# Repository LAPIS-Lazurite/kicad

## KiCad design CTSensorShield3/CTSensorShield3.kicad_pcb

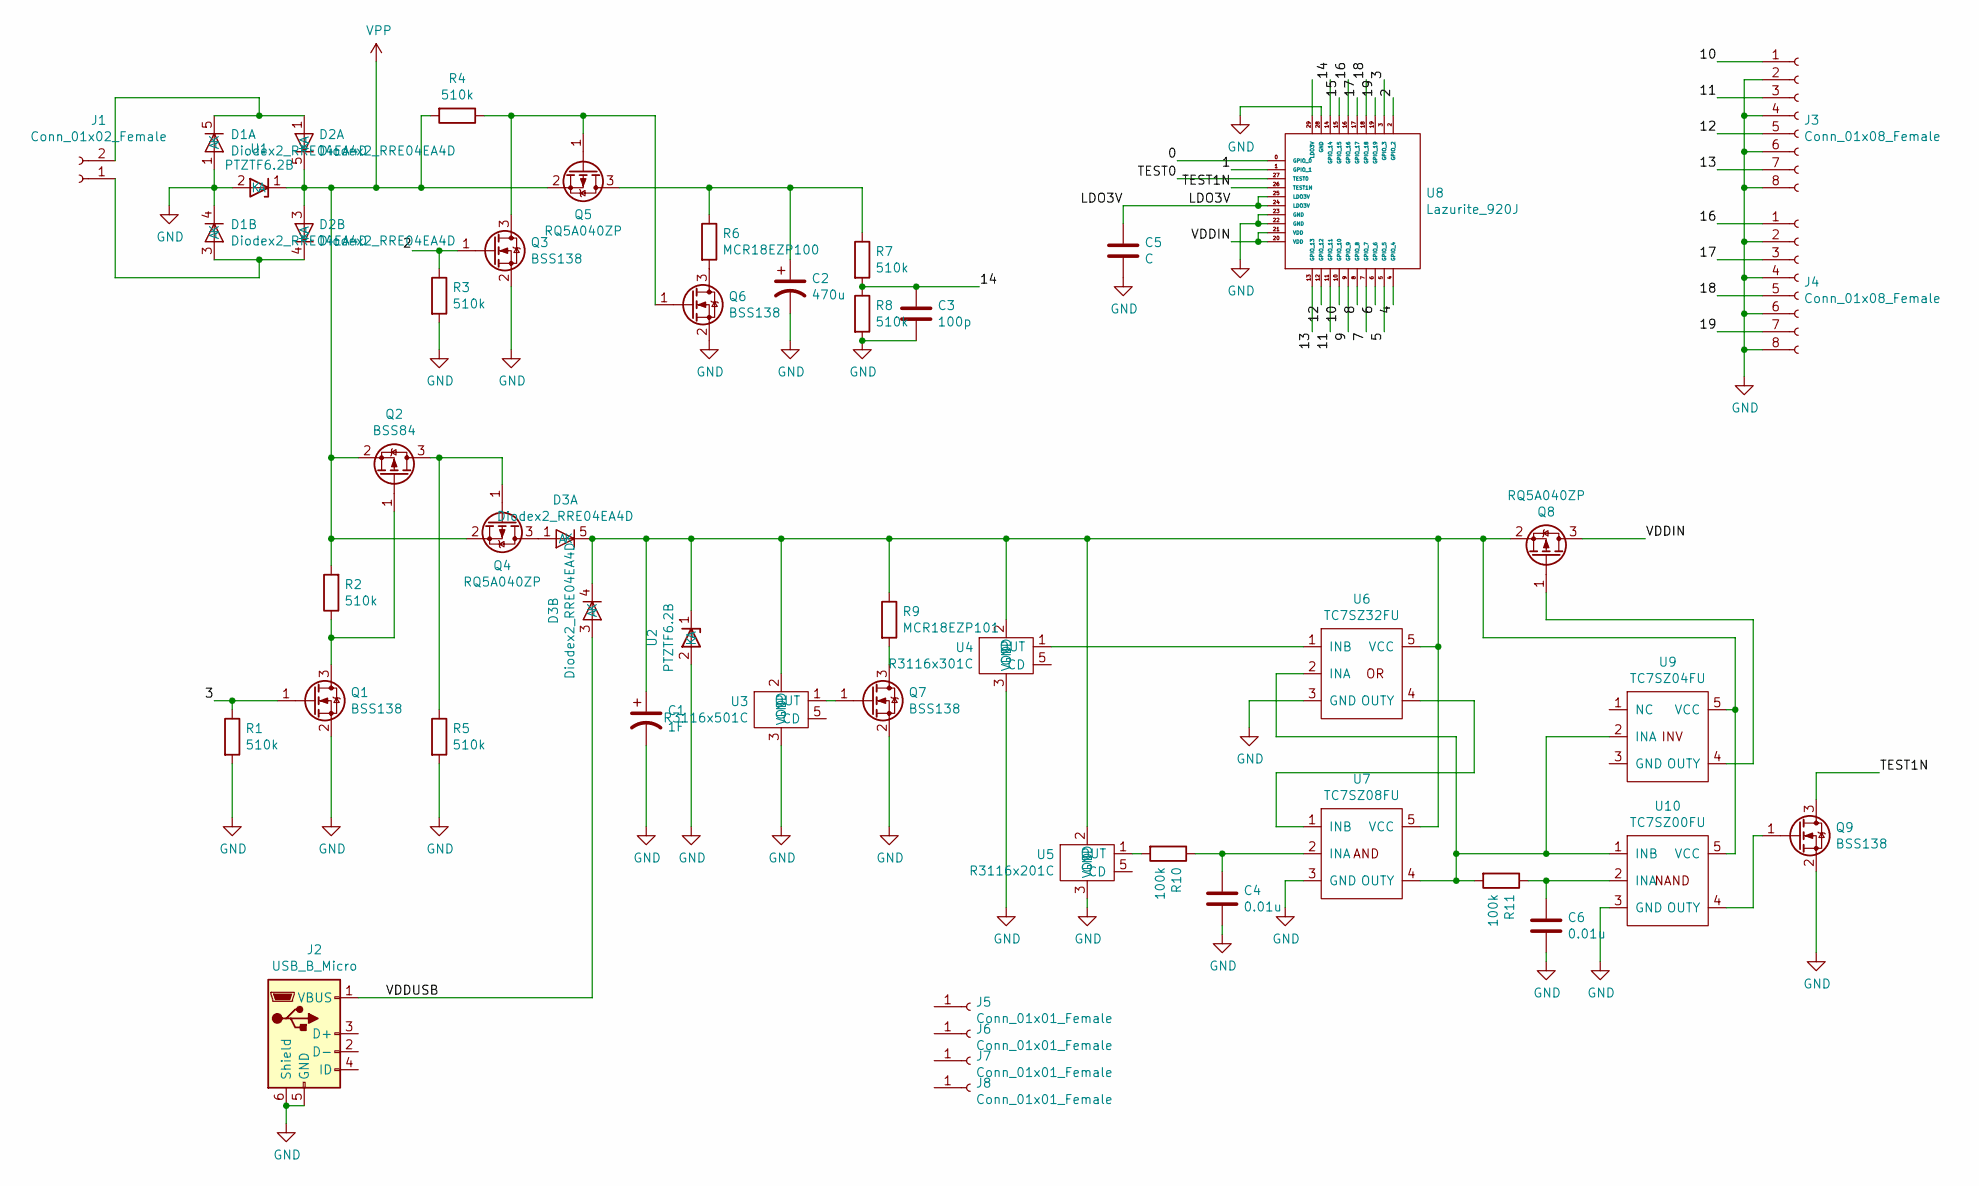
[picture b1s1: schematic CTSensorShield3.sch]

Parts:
C1: 1F; CP_Radial_D20.5mm_P5.50mm
C2: 470u; CP_Radial_D8.0mm_P3.50mm
C3: 100p; C_0402_1005Metric
C4, C6: 0.01u; C_0402_1005Metric
C5: C; C_0402_1005Metric
D1, D2, D3: Diodex2_RRE04EA4D; TSMD5
J1: Conn_01x02_Female; XW4E-02B1-V1
J2: USB_B_Micro; USB_B_hirose_ZX62R-B-5P
J3, J4: Conn_01x08_Female; XW4E-08B1-V1
J5, J6, J7, J8: Conn_01x01_Female; MountingHole_2.7mm_M2.5
Q1, Q3, Q6, Q7, Q9: BSS138; SOT-23
Q2: BSS84; SOT-23
Q4, Q5, Q8: RQ5A040ZP; SOT-346T
R1, R2, R3, R4, R5, R7, R8: 510k; R_0402_1005Metric
R6: MCR18EZP100; R_1206_3216Metric
R9: MCR18EZP101; R_1206_3216Metric
R10, R11: 100k; R_0402_1005Metric
U1, U2: PTZTF6.2B; DO-214AC
U3: R3116x501C; SOT-23-5
U4: R3116x301C; SOT-23-5
U5: R3116x201C; SOT-23-5
U6: TC7SZ32FU; SOT-353_SC-70-5
U7: TC7SZ08FU; SOT-353_SC-70-5
U8: Lazurite_920J; 920J
U9: TC7SZ04FU; SOT-353_SC-70-5
U10: TC7SZ00FU; SOT-353_SC-70-5

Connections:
/0: U8.0 (GPIO_0)
/1: U8.1 (GPIO_1)
/2: Q3.1 (G), R3.1, U8.2 (GPIO_2)
/3: Q1.1 (G), R1.1, U8.3 (GPIO_3)
/4: U8.4 (GPIO_4)
/5: U8.5 (GPIO_5)
/6: U8.6 (GPIO_6)
/7: U8.7 (GPIO_7)
/8: U8.8 (GPIO_8)
/9: U8.9 (GPIO_9)
/10: J3.1, U8.10 (GPIO_10)
/11: J3.3, U8.11 (GPIO_11)
/12: J3.5, U8.12 (GPIO_12)
/13: J3.7, U8.13 (GPIO_13)
/14: C3.1, R7.2, R8.1, U8.14 (GPIO_14)
/15: U8.15 (GPIO_15)
/16: J4.1, U8.16 (GPIO_16)
/17: J4.3, U8.17 (GPIO_17)
/18: J4.5, U8.18 (GPIO_18)
/19: J4.7, U8.19 (GPIO_19)
/LDO3V: C5.1, U8.24 (LDO3V), U8.25 (LDO3V)
/TEST0: U8.27 (TEST0)
/TEST1N: Q9.3 (D), U8.26 (TEST1N)
/VDDIN: Q8.3 (D), U8.20 (VDD), U8.21 (VDD)
/VDDUSB: D3.3 (K), J2.1 (VBUS)
GND: C1.2, C2.2, C3.2, C4.2, C5.2, C6.2, D1.1 (K), D1.4 (A), J2.5 (GND), J2.6 (Shield), J3.2, J3.4, J3.6, J3.8, J4.2, J4.4, J4.6, J4.8, Q1.2 (S), Q3.2 (S), Q6.2 (S), Q7.2 (S), Q9.2 (S), R1.2, R3.2, R5.2, R8.2, U1.2 (A), U2.2 (A), U3.3 (GND), U4.3 (GND), U5.3 (GND), U6.3 (GND), U7.3 (GND), U8.22 (GND), U8.23 (GND), U8.28 (GND), U10.3 (GND)
unnamed: C1.1, D3.4 (A), D3.5 (A), Q8.2 (S), R9.1, U2.1 (K), U3.2 (VDD), U4.2 (VDD), U5.2 (VDD), U6.5 (VCC), U7.5 (VCC), U9.5 (VCC), U10.5 (VCC)
unnamed: C2.1, Q5.3 (D), R6.1, R7.1
unnamed: C4.1, R10.1, U7.2 (INA)
unnamed: C6.1, R11.1, U10.2 (INA)
unnamed: D1.3 (K), D2.4 (A), J1.1
unnamed: D1.5 (A), D2.1 (K), J1.2
unnamed: D3.1 (K), Q4.3 (D)
unnamed: Q1.3 (D), Q2.1 (G), R2.1
unnamed: Q2.3 (D), Q4.1 (G), R5.1
unnamed: Q3.3 (D), Q5.1 (G), Q6.1 (G), R4.1
unnamed: Q6.3 (D), R6.2
unnamed: Q7.1 (G), U3.1 (OUT)
unnamed: Q7.3 (D), R9.2
unnamed: Q8.1 (G), U9.4 (OUTY)
unnamed: Q9.1 (G), U10.4 (OUTY)
unnamed: R10.2, U5.1 (OUT)
unnamed: R11.2, U6.2 (INA), U7.4 (OUTY), U9.2 (INA), U10.1 (INB)
unnamed: U4.1 (OUT), U6.1 (INB)
unnamed: U6.4 (OUTY), U7.1 (INB)
VPP: D2.3 (K), D2.5 (A), Q2.2 (S), Q4.2 (S), Q5.2 (S), R2.2, R4.2, U1.1 (K)

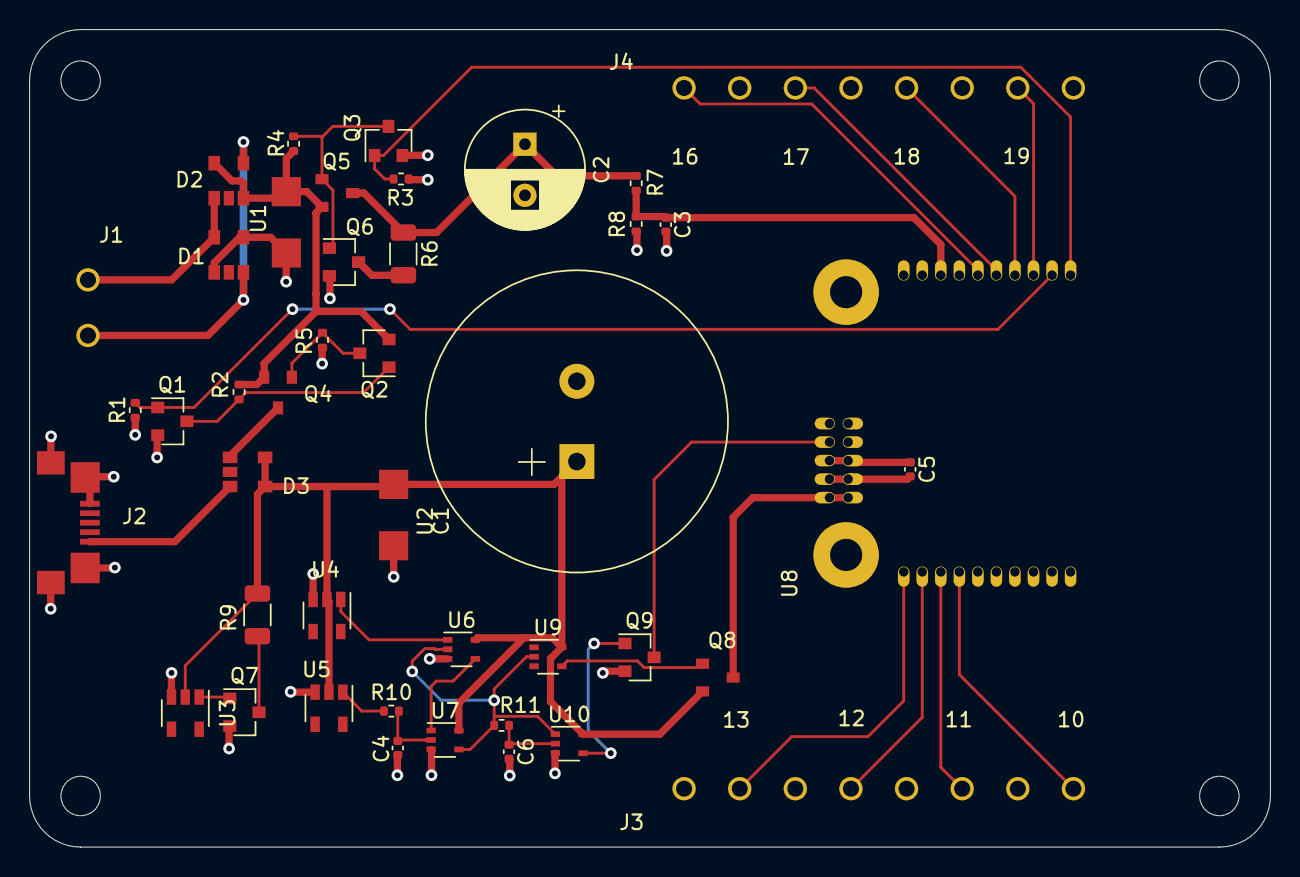
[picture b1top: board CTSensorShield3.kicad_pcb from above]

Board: 2 copper layers, 85.0 x 56.0 mm, 47 parts (0 on the bottom side), 36 nets.

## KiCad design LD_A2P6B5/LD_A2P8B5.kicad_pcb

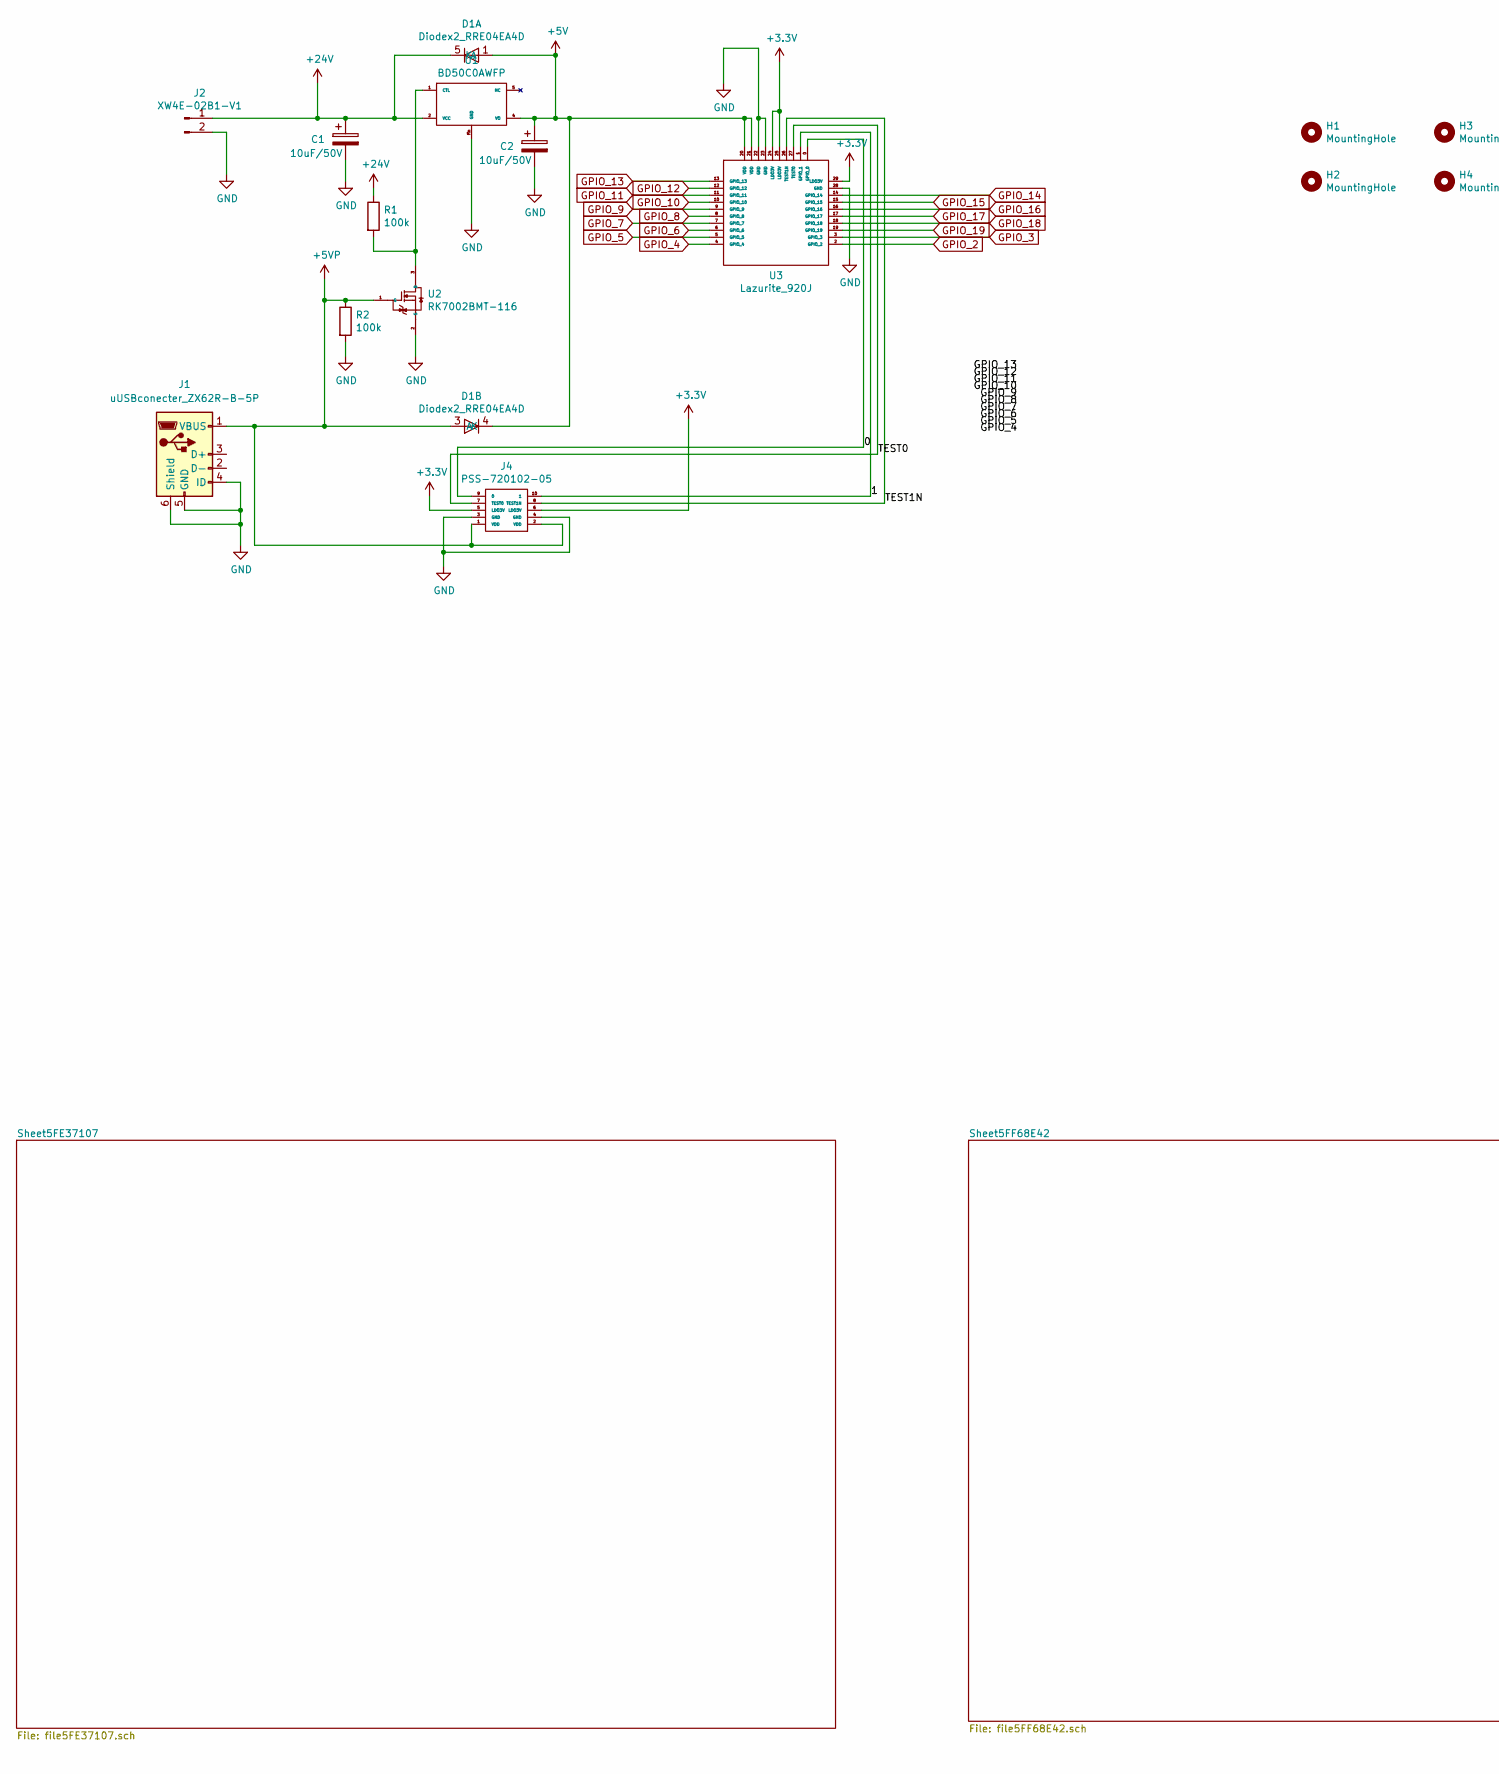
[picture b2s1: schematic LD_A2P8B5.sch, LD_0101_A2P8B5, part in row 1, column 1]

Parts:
C1, C2: 10uF/50V; C_1210_3225Metric
D1: Diodex2_RRE04EA4D; SOT-25T
H1, H2, H3, H4: MountingHole; MountingHole_2.2mm_M2
J1: uUSBconecter_ZX62R-B-5P; USB_B_hirose_ZX62R-B-5P
J2: XW4E-02B1-V1
J4: PSS-720102-05
R1, R2: 100k; R_0402_1005Metric
U1: BD50C0AWFP; TO252-5
U2: RK7002BMT-116; SOT-23
U3: Lazurite_920J; 920J

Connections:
+3V3: J4.5 (LDO3V), J4.6 (LDO3V), U3.24 (LDO3V), U3.25 (LDO3V), U3.29 (LDO3V); also elsewhere on the board
+5V: C2.1, D1.1 (K), D1.4 (A), U1.4 (VO), U3.20 (VDD), U3.21 (VDD); also elsewhere on the board
+5VP: D1.3 (K), J1.1 (VBUS), J4.1 (VDD), J4.2 (VDD), R2.1, U2.1 (G)
+24V: C1.1, D1.5 (A), J2.1, R1.1, U1.2 (VCC); also elsewhere on the board
/0: J4.9 (0), U3.0 (GPIO_0)
/1: J4.10 (1), U3.1 (GPIO_1)
/TEST0: J4.7 (TEST0), U3.27 (TEST0)
/TEST1N: J4.8 (TEST1N), U3.26 (TEST1N)
GND: C1.2, C2.2, J1.4 (ID), J1.5 (GND), J1.6 (Shield), J2.2, J4.3 (GND), J4.4 (GND), R2.2, U1.fin (GND), U2.2 (S), U3.22 (GND), U3.23 (GND), U3.28 (GND); also elsewhere on the board
GPIO_2: U3.2 (GPIO_2); also elsewhere on the board
GPIO_3: U3.3 (GPIO_3); also elsewhere on the board
GPIO_4: U3.4 (GPIO_4); also elsewhere on the board
GPIO_5: U3.5 (GPIO_5); also elsewhere on the board
GPIO_6: U3.6 (GPIO_6); also elsewhere on the board
GPIO_7: U3.7 (GPIO_7); also elsewhere on the board
GPIO_8: U3.8 (GPIO_8); also elsewhere on the board
GPIO_9: U3.9 (GPIO_9); also elsewhere on the board
GPIO_10: U3.10 (GPIO_10); also elsewhere on the board
GPIO_11: U3.11 (GPIO_11); also elsewhere on the board
GPIO_12: U3.12 (GPIO_12); also elsewhere on the board
GPIO_13: U3.13 (GPIO_13); also elsewhere on the board
GPIO_14: U3.14 (GPIO_14); also elsewhere on the board
GPIO_15: U3.15 (GPIO_15); also elsewhere on the board
GPIO_16: U3.16 (GPIO_16); also elsewhere on the board
GPIO_17: U3.17 (GPIO_17); also elsewhere on the board
GPIO_18: U3.18 (GPIO_18); also elsewhere on the board
GPIO_19: U3.19 (GPIO_19); also elsewhere on the board
unnamed: R1.2, U1.1 (CTL), U2.3 (D)

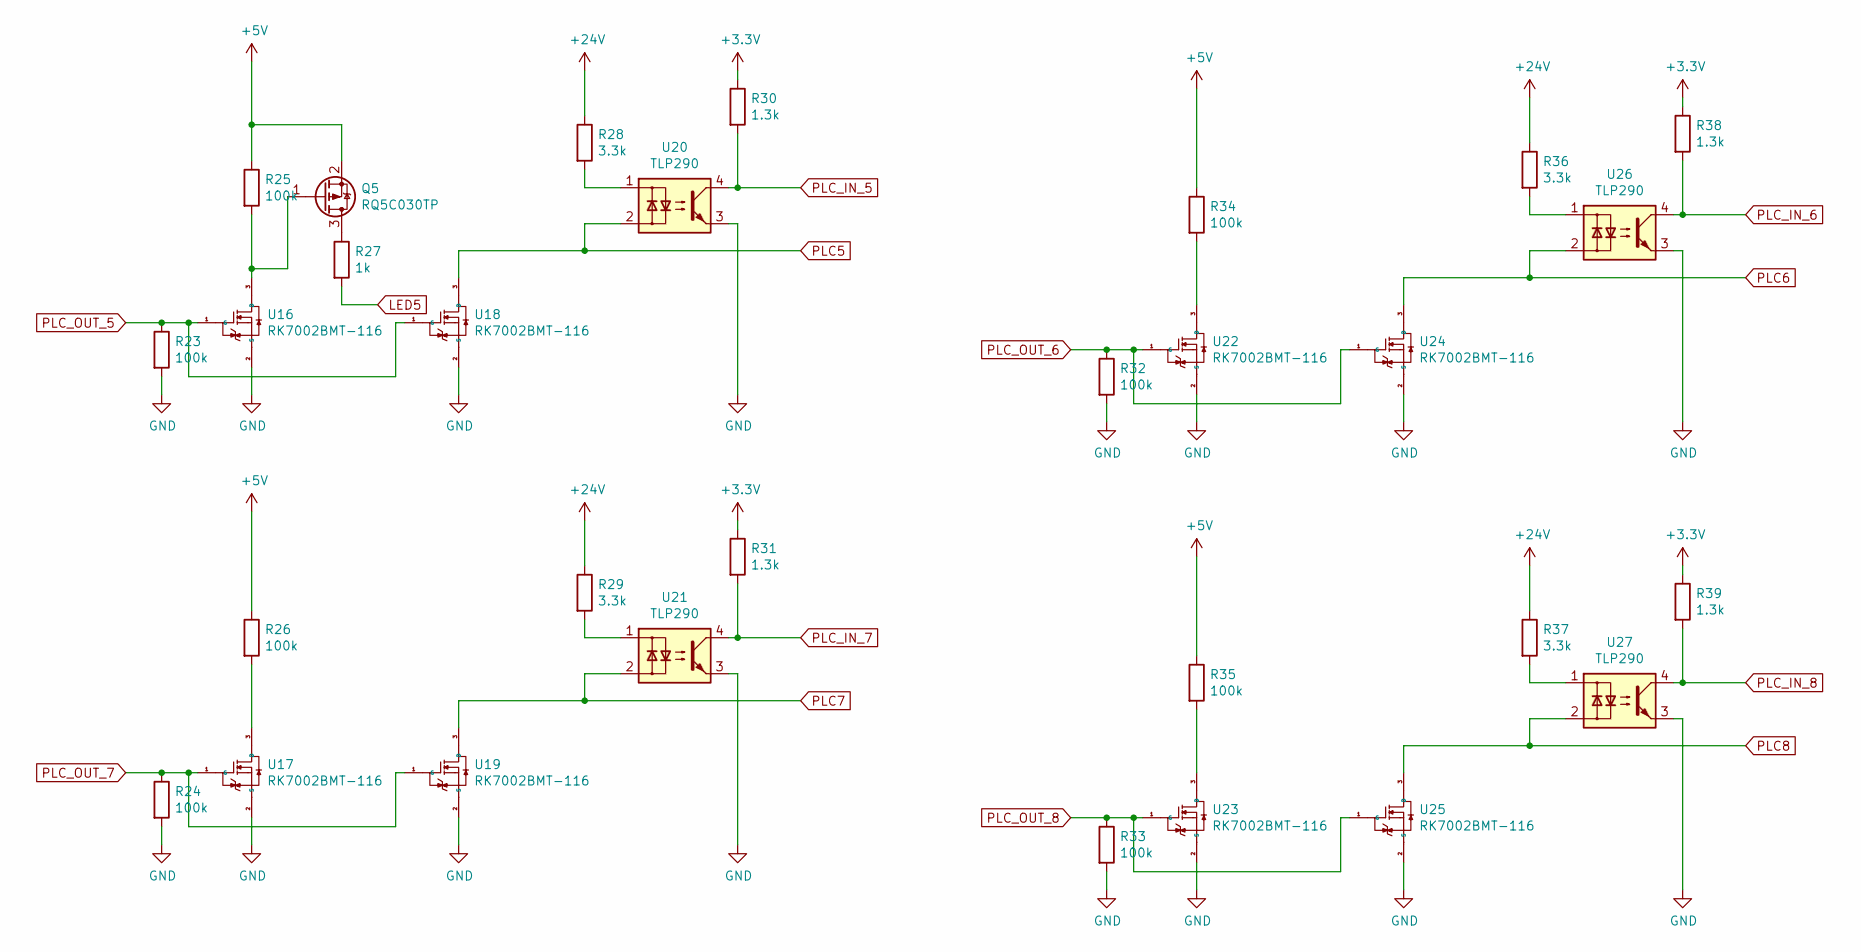
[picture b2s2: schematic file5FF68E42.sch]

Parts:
Q5: RQ5C030TP; SOT-346T
R23, R24, R25, R26, R32, R33, R34, R35: 100k; R_0402_1005Metric
R27: 1k; R_0402_1005Metric
R28, R29, R36, R37: 3.3k; R_0402_1005Metric
R30, R31, R38, R39: 1.3k; R_0402_1005Metric
U16, U17, U18, U19, U22, U23, U24, U25: RK7002BMT-116; SOT-23
U20, U21, U26, U27: TLP290; SOP-4_4.4x2.6mm_P1.27mm

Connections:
+3V3: R30.1, R31.1, R38.1, R39.1; also elsewhere on the board
+5V: Q5.2 (S), R25.1, R26.1, R34.1, R35.1; also elsewhere on the board
+24V: R28.1, R29.1, R36.1, R37.1; also elsewhere on the board
GND: R23.2, R24.2, R32.2, R33.2, U16.2 (S), U17.2 (S), U18.2 (S), U19.2 (S), U20.3, U21.3, U22.2 (S), U23.2 (S), U24.2 (S), U25.2 (S), U26.3, U27.3; also elsewhere on the board
LED5: R27.2; also elsewhere on the board
unnamed: Q5.1 (G), R25.2, U16.3 (D)
unnamed: Q5.3 (D), R27.1
unnamed: R26.2, U17.3 (D)
unnamed: R28.2, U20.1
unnamed: R29.2, U21.1
unnamed: R34.2, U22.3 (D)
unnamed: R35.2, U23.3 (D)
unnamed: R36.2, U26.1
unnamed: R37.2, U27.1
PLC5: U18.3 (D), U20.2; also elsewhere on the board
PLC6: U24.3 (D), U26.2; also elsewhere on the board
PLC7: U19.3 (D), U21.2; also elsewhere on the board
PLC8: U25.3 (D), U27.2; also elsewhere on the board
PLC_IN_5: R30.2, U20.4; also elsewhere on the board
PLC_IN_6: R38.2, U26.4; also elsewhere on the board
PLC_IN_7: R31.2, U21.4; also elsewhere on the board
PLC_IN_8: R39.2, U27.4; also elsewhere on the board
PLC_OUT_5: R23.1, U16.1 (G), U18.1 (G); also elsewhere on the board
PLC_OUT_6: R32.1, U22.1 (G), U24.1 (G); also elsewhere on the board
PLC_OUT_7: R24.1, U17.1 (G), U19.1 (G); also elsewhere on the board
PLC_OUT_8: R33.1, U23.1 (G), U25.1 (G); also elsewhere on the board

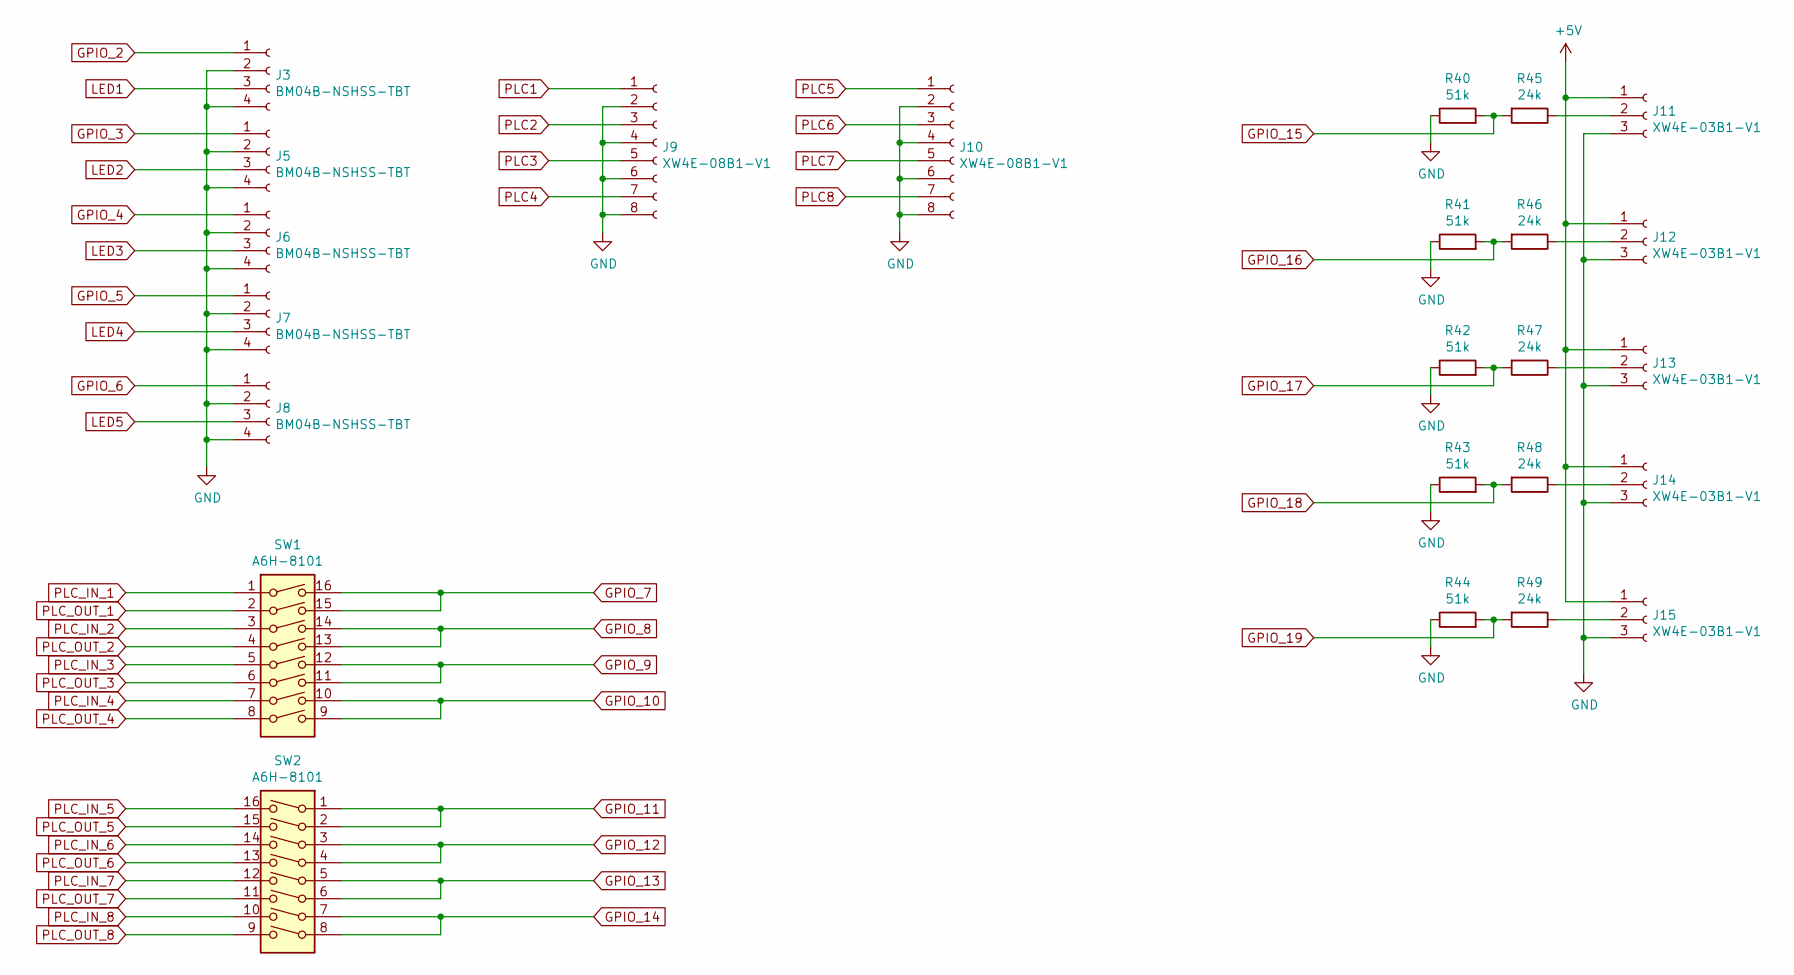
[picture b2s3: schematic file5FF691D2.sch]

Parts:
J3, J5, J6, J7, J8: BM04B-NSHSS-TBT; JST_NSH_SM04B_1mm_Vertical
J9, J10: XW4E-08B1-V1
J11, J12, J13, J14, J15: XW4E-03B1-V1
R40, R41, R42, R43, R44: 51k; R_0402_1005Metric
R45, R46, R47, R48, R49: 24k; R_0402_1005Metric
SW1, SW2: A6H-8101

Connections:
+5V: J11.1, J12.1, J13.1, J14.1, J15.1; also elsewhere on the board
GND: J3.2, J3.4, J5.2, J5.4, J6.2, J6.4, J7.2, J7.4, J8.2, J8.4, J9.2, J9.4, J9.6, J9.8, J10.2, J10.4, J10.6, J10.8, J11.3, J12.3, J13.3, J14.3, J15.3, R40.1, R41.1, R42.1, R43.1, R44.1; also elsewhere on the board
GPIO_2: J3.1; also elsewhere on the board
GPIO_3: J5.1; also elsewhere on the board
GPIO_4: J6.1; also elsewhere on the board
GPIO_5: J7.1; also elsewhere on the board
GPIO_6: J8.1; also elsewhere on the board
GPIO_7: SW1.15, SW1.16; also elsewhere on the board
GPIO_8: SW1.13, SW1.14; also elsewhere on the board
GPIO_9: SW1.11, SW1.12; also elsewhere on the board
GPIO_10: SW1.9, SW1.10; also elsewhere on the board
GPIO_11: SW2.1, SW2.2; also elsewhere on the board
GPIO_12: SW2.3, SW2.4; also elsewhere on the board
GPIO_13: SW2.5, SW2.6; also elsewhere on the board
GPIO_14: SW2.7, SW2.8; also elsewhere on the board
GPIO_15: R40.2, R45.2; also elsewhere on the board
GPIO_16: R41.2, R46.2; also elsewhere on the board
GPIO_17: R42.2, R47.2; also elsewhere on the board
GPIO_18: R43.2, R48.2; also elsewhere on the board
GPIO_19: R44.2, R49.2; also elsewhere on the board
LED1: J3.3; also elsewhere on the board
LED2: J5.3; also elsewhere on the board
LED3: J6.3; also elsewhere on the board
LED4: J7.3; also elsewhere on the board
LED5: J8.3; also elsewhere on the board
unnamed: J11.2, R45.1
unnamed: J12.2, R46.1
unnamed: J13.2, R47.1
unnamed: J14.2, R48.1
unnamed: J15.2, R49.1
PLC1: J9.1; also elsewhere on the board
PLC2: J9.3; also elsewhere on the board
PLC3: J9.5; also elsewhere on the board
PLC4: J9.7; also elsewhere on the board
PLC5: J10.1; also elsewhere on the board
PLC6: J10.3; also elsewhere on the board
PLC7: J10.5; also elsewhere on the board
PLC8: J10.7; also elsewhere on the board
PLC_IN_1: SW1.1; also elsewhere on the board
PLC_IN_2: SW1.3; also elsewhere on the board
PLC_IN_3: SW1.5; also elsewhere on the board
PLC_IN_4: SW1.7; also elsewhere on the board
PLC_IN_5: SW2.16; also elsewhere on the board
PLC_IN_6: SW2.14; also elsewhere on the board
PLC_IN_7: SW2.12; also elsewhere on the board
PLC_IN_8: SW2.10; also elsewhere on the board
PLC_OUT_1: SW1.2; also elsewhere on the board
PLC_OUT_2: SW1.4; also elsewhere on the board
PLC_OUT_3: SW1.6; also elsewhere on the board
PLC_OUT_4: SW1.8; also elsewhere on the board
PLC_OUT_5: SW2.15; also elsewhere on the board
PLC_OUT_6: SW2.13; also elsewhere on the board
PLC_OUT_7: SW2.11; also elsewhere on the board
PLC_OUT_8: SW2.9; also elsewhere on the board

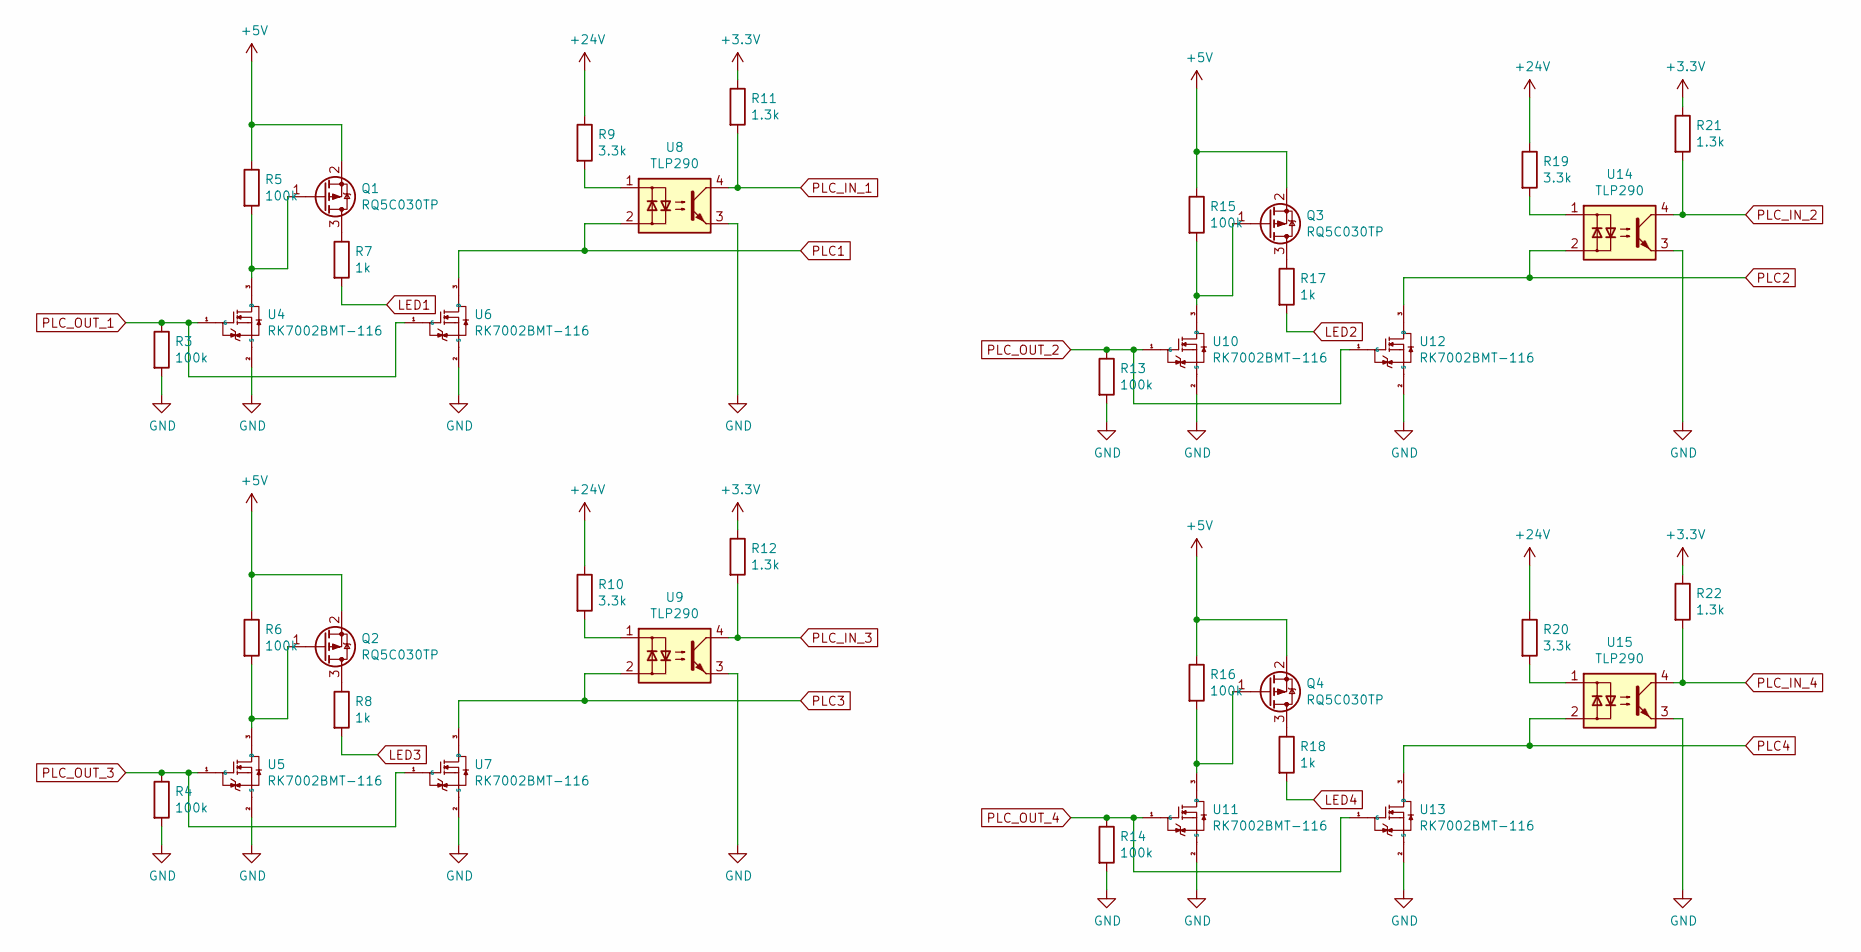
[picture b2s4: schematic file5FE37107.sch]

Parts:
Q1, Q2, Q3, Q4: RQ5C030TP; SOT-346T
R3, R4, R5, R6, R13, R14, R15, R16: 100k; R_0402_1005Metric
R7, R8, R17, R18: 1k; R_0402_1005Metric
R9, R10, R19, R20: 3.3k; R_0402_1005Metric
R11, R12, R21, R22: 1.3k; R_0402_1005Metric
U4, U5, U6, U7, U10, U11, U12, U13: RK7002BMT-116; SOT-23
U8, U9, U14, U15: TLP290; SOP-4_4.4x2.6mm_P1.27mm

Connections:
+3V3: R11.1, R12.1, R21.1, R22.1; also elsewhere on the board
+5V: Q1.2 (S), Q2.2 (S), Q3.2 (S), Q4.2 (S), R5.1, R6.1, R15.1, R16.1; also elsewhere on the board
+24V: R9.1, R10.1, R19.1, R20.1; also elsewhere on the board
GND: R3.2, R4.2, R13.2, R14.2, U4.2 (S), U5.2 (S), U6.2 (S), U7.2 (S), U8.3, U9.3, U10.2 (S), U11.2 (S), U12.2 (S), U13.2 (S), U14.3, U15.3; also elsewhere on the board
LED1: R7.2; also elsewhere on the board
LED2: R17.2; also elsewhere on the board
LED3: R8.2; also elsewhere on the board
LED4: R18.2; also elsewhere on the board
unnamed: Q1.1 (G), R5.2, U4.3 (D)
unnamed: Q1.3 (D), R7.1
unnamed: Q2.1 (G), R6.2, U5.3 (D)
unnamed: Q2.3 (D), R8.1
unnamed: Q3.1 (G), R15.2, U10.3 (D)
unnamed: Q3.3 (D), R17.1
unnamed: Q4.1 (G), R16.2, U11.3 (D)
unnamed: Q4.3 (D), R18.1
unnamed: R9.2, U8.1
unnamed: R10.2, U9.1
unnamed: R19.2, U14.1
unnamed: R20.2, U15.1
PLC1: U6.3 (D), U8.2; also elsewhere on the board
PLC2: U12.3 (D), U14.2; also elsewhere on the board
PLC3: U7.3 (D), U9.2; also elsewhere on the board
PLC4: U13.3 (D), U15.2; also elsewhere on the board
PLC_IN_1: R11.2, U8.4; also elsewhere on the board
PLC_IN_2: R21.2, U14.4; also elsewhere on the board
PLC_IN_3: R12.2, U9.4; also elsewhere on the board
PLC_IN_4: R22.2, U15.4; also elsewhere on the board
PLC_OUT_1: R3.1, U4.1 (G), U6.1 (G); also elsewhere on the board
PLC_OUT_2: R13.1, U10.1 (G), U12.1 (G); also elsewhere on the board
PLC_OUT_3: R4.1, U5.1 (G), U7.1 (G); also elsewhere on the board
PLC_OUT_4: R14.1, U11.1 (G), U13.1 (G); also elsewhere on the board

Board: 2 copper layers, 105 parts (0 on the bottom side), 83 nets, no tracks yet.

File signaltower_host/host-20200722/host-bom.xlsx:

ID | 参照記号 | パッケージ | 数 | 名称 | Supplier and ref | 必要数ヒツヨウスウ
1 | REF** | Lazurite_logo | 1 | Lazurite_logo | 部品無しブヒｎ ナシ
2 | H4,H3,H2,H1 | MountingHole_2.2mm_M2 | 4 | MountingHole | 部品無しブヒｎ ナシ
3 | J3 | JST_NSH_SM06B_1mm_Horizonal | 1 | Conn_01x06_Female | JST製 NSH_SM06B-NSHSS-TBセイ
4 | U3 | 920J | 1 | Lazurite_920J | 廣杉計器のコネクタ（FSS-71034-10 2pcs/FSS-72034-05 1pcs)ヒロスギケイキ
5 | J4 | PSS-720102-05 | 1 | PSS-720102-05 | 廣杉計器 PSS-720102-05ヒロスギケイキ
6 | U1 | LDO_TO252-5 | 1 | BD50C0AWFP | 支給部品シキュウブヒｎ | 50
7 | J2 | GB-50LBS-2P | 1 | GB-TB-50LBS-2P | https://www.marutsu.co.jp/pc/i/594913/
8 | U2 | ROHM_MOSFET_SOT-23 | 1 | RK7002BMT-116 | 支給部品シキュウブヒｎ | 50
9 | J1 | USB_B_hirose_ZX62R-B-5P | 1 | uUSBconecter_ZX62R-B-5P | 指定なしシテイナシ
10 | D1 | Diode_SOT-25T | 1 | Diodex2_RRE04EA4D | 支給部品シキュウブヒｎ | 在庫ありザイコアリ
11 | R1,R2 | R_0402_1005Metric | 2 | 100k | 指定なしシテイナシ
12 | C2,C1 | C_1210_3225Metric | 2 | 10uF/50V | 指定なしシテイナシ

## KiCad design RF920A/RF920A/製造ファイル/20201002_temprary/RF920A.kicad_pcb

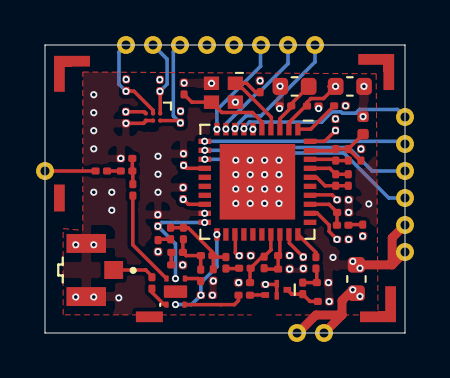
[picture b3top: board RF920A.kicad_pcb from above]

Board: 4 copper layers, 20.0 x 16.0 mm, 77 parts (0 on the bottom side), 45 nets.

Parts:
C1: 10uF; C_0603_1608Metric
C5, C17, C18, C22, C24, C25, C29, C31, C32: 0.1u; C_0201_0603Metric
C10, C12, C45, C46: 1000p; C_0201_0603Metric
C11, C13: 10u; C_0603_1608Metric
C15, C16, C33, C43: NC; C_0201_0603Metric
C19: 1u; C_0402_1005Metric
C20, C34, C38: 100p; C_0201_0603Metric
C21, C42, C44: 0.01u; C_0201_0603Metric
C23: 4.7p; C_0201_0603Metric
C26, C47, C48: 47p; C_0201_0603Metric
C28: 3.3n; C_0201_0603Metric
C35: 3.0p; C_0201_0603Metric
C36: 0.6p; C_0201_0603Metric
C37: 1u; C_0201_0603Metric
C39: 2.4p; C_0201_0603Metric
C40: 0.9p; C_0201_0603Metric
C41: 0.5p; C_0201_0603Metric
J1, J2, J3, J4, J5, J6, J7, J8, J9, J10, J11, J12, J13, J14, J16, J17, J19: Conn_01x01; LGAPAD
L1: 4.3n; L_0201_0603Metric
L2: 10n; L_0201_0603Metric
L3: 13n; L_0201_0603Metric
L4, L8: NC; L_0201_0603Metric
L5: 15n; L_0201_0603Metric
L6, L7: 6.2n; L_0201_0603Metric
L9: 2.2n; L_0201_0603Metric
L10: 0.039u; L_0201_0603Metric
L11: 6.8n; L_0201_0603Metric
R5, R6, R7: 10k; R_0201_0603Metric
R8: 51; R_0201_0603Metric
R9: 8.2k; R_0201_0603Metric
U1: ML7396D; WQFN-40-1EP_6x6mm_P0.5mm_EP4.2x4.2mm
U2: MHF1; IPEX_20279-001E-03
U3: SKY13438-374LF; SKY13438_374LF
U4: WFD79C0925FG
U5: NX2016S; NX2016SA
U6: BRCB032GWZ-3; UCSP30L1

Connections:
+3.3VA: C1.2, C18.1, C31.1, J13.1, J14.1, U1.29, U1.40
+3V3: C5.1, C22.2, C25.2, J2.1, J3.1, R5.1, R6.1, R7.2, U1.14, U1.18, U6.A3
/REGPDIN: J9.1, U1.8
/RESETN: J10.1, U1.7
/SCEN: J5.1, U1.12
/SCL: J12.1, R6.2, U6.A1
/SCLK: J6.1, U1.11
/SDA: J19.1, R5.2, U6.B1
/SDI: J4.1, U1.13
/SDO: J8.1, U1.9
/SINTN: J7.1, U1.10
/VDDCP: C10.1, C11.2, C24.1, C29.2, C32.2, U1.2, U1.23, U1.32, U1.34
/WP: J11.1, R7.1, U6.A2
/XT+: C15.2, U1.4, U5.1
/XT-: C16.1, U1.5, U5.3
GND: C1.1, C5.2, C10.2, C11.1, C12.2, C13.1, C15.1, C16.2, C17.1, C18.2, C19.1, C22.1, C24.2, C25.1, C26.2, C28.2, C29.1, C31.2, C32.1, C33.2, C37.2, C38.1, C39.2, C40.2, C43.2, C45.2, C46.1, J16.1, J17.1, L3.2, L4.2, L11.1, R8.2, U1.6, U1.19, U1.41, U2.2, U2.3, U4.2, U4.3, U4.5, U5.2, U5.4, U6.B2, U6.B3
unnamed: C12.1, C13.2, U1.3
unnamed: C17.2, U1.1
unnamed: C19.2, C20.1, C21.2, R8.1, U1.39
unnamed: C20.2, C21.1, U1.38
unnamed: C23.1, L1.1, U1.36
unnamed: C23.2, L1.2, U1.37
unnamed: C26.1, R9.1, U1.33
unnamed: C28.1, R9.2
unnamed: C33.1, C35.1, L2.1, U1.27
unnamed: C34.1, U1.30
unnamed: C34.2, C36.1, L3.1
unnamed: C35.2, L5.2
unnamed: C36.2, L4.1, U4.1
unnamed: C37.1, C38.2, L2.2, U1.28
unnamed: C39.1, C41.2, L5.1, L6.1, L7.2
unnamed: C40.1, L6.2
unnamed: C41.1, C44.1, L7.1, L8.1
unnamed: C42.1, U4.4
unnamed: C42.2, U3.3
unnamed: C43.1, L8.2
unnamed: C44.2, U3.4
unnamed: C45.1, U1.21, U3.2
unnamed: C46.2, U1.20, U3.5
unnamed: C47.1, U3.6
unnamed: C47.2, L10.2, L11.2
unnamed: C48.1, U2.1
unnamed: C48.2, U3.1
unnamed: J1.1, L9.1
unnamed: L9.2, L10.1

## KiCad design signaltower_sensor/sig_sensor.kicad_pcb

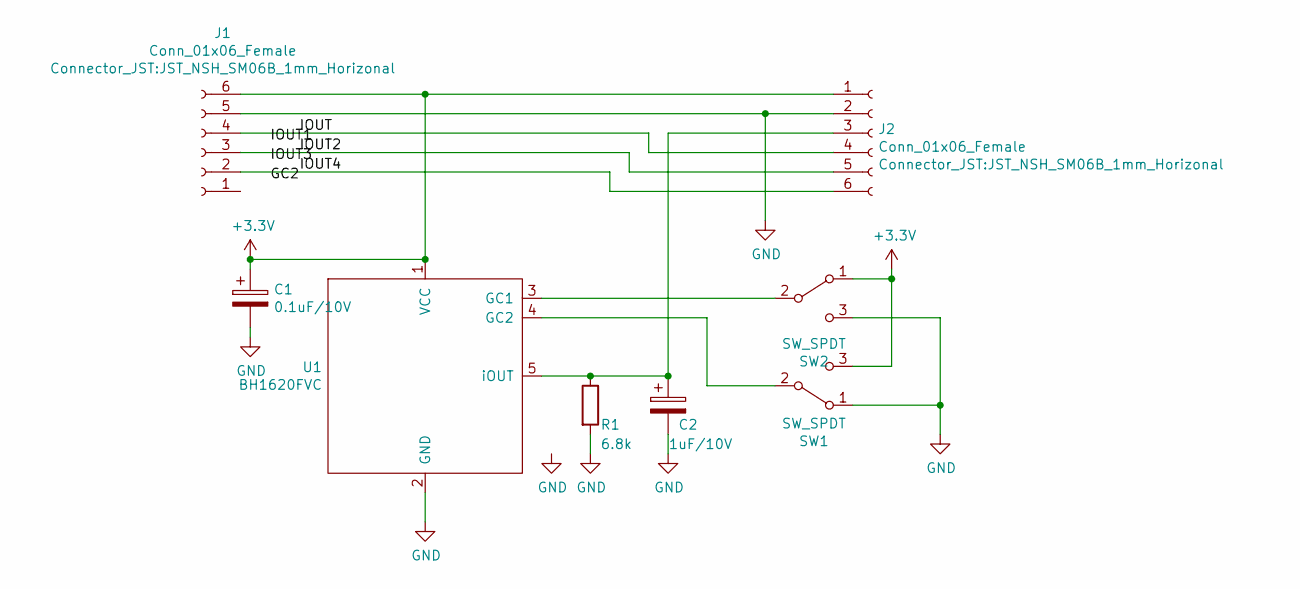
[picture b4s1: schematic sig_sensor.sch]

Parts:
C1: 0.1uF/10V; C_0201_0603Metric
C2: 1uF/10V; C_0201_0603Metric
J1, J2: Conn_01x06_Female; JST_NSH_SM06B_1mm_Horizonal
R1: 6.8k; R_0402_1005Metric
SW1, SW2: SW_SPDT; SHORT_SPDT
U1: BH1620FVC; wsof5

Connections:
+3V3: C1.1, J1.6, J2.1, SW1.3 (C), SW2.1 (A), U1.1 (VCC)
/IOUT: J1.4, J2.4
/IOUT2: J1.3, J2.5
/IOUT4: J1.2, J2.6
GND: C1.2, C2.2, J1.5, J2.2, R1.2, SW1.1 (A), SW2.3 (C), U1.2 (GND)
unnamed: C2.1, J2.3, R1.1, U1.5 (iOUT)
unnamed: SW1.2 (B), U1.4 (GC2)
unnamed: SW2.2 (B), U1.3 (GC1)

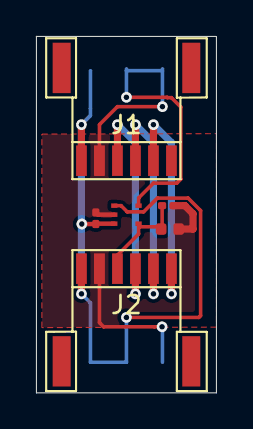
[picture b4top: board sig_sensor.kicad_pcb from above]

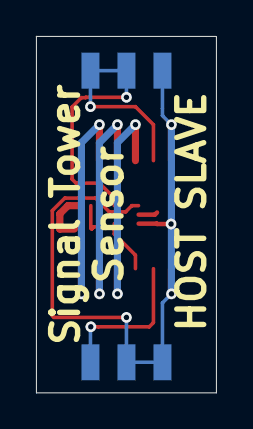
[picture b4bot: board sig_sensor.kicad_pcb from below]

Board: 2 copper layers, 10.0 x 19.8 mm, 8 parts (2 on the bottom side), 8 nets.

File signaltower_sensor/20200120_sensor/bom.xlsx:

ID | 参照記号 | パッケージ | 数 | 名称 | Supplier and ref
1 | J1 | FFC-FPC_5051100892 | 1 | 5051100892_FFC-FPC_in
2 | J2 | FFC-FPC_5051100892 | 1 | 5051100892_FFC-FPC_out
3 | U1 | wsof5 | 1 | BH1620FVC | 支給部品シキュウブヒン
4 | R1 | R_0402_1005Metric | 1 | 6.8k | 1005
5 | C2 | C_0201_0603Metric | 1 | 1uF/10V | 0603
6 | C1 | C_0201_0603Metric | 1 | 0.1uF/10V | 0603
